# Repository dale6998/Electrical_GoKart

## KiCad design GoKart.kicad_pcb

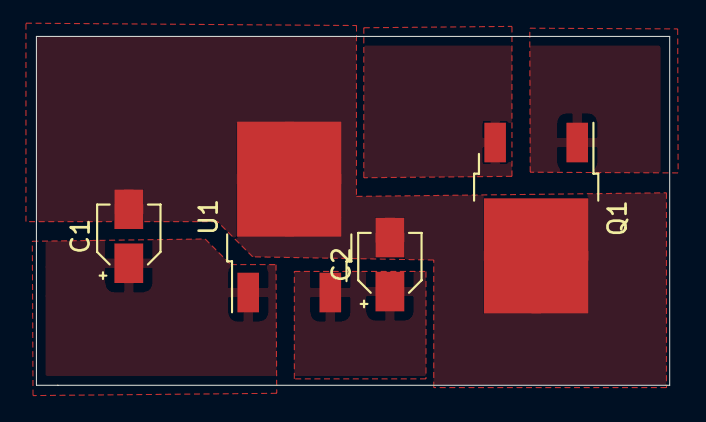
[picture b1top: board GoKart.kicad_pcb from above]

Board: 2 copper layers, 35.2 x 19.4 mm, 4 parts (0 on the bottom side), 3 nets, no tracks yet.

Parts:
C1, C2: CP1_Small; CP_Elec_3x5.3
Q1: Q_NMOS_GSD; TO-252-2
U1: LM7805CT_Obsolete; TO-252-2

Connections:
+5V: C2.1, U1.3 (OUT)
+BATT: C1.1, U1.1 (IN)
GND: C1.2, C2.2, Q1.2 (S), U1.2 (GND)
